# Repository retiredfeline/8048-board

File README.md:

# 8048 board

This is the circuit design for a board using the 8048 MCU, initially intended to be a clock but can be used for other purposes. It can drive multiplexed 7 segment LEDs or a serial interface display using the TM1637 chip. The timer reference can be the onboard crystal, a DS128(8)7 clock chip, or mains.

In retrospect 7407s are probably better for the output buffers because if their input is high or floating, say the 8048 chip is removed, their output transistors will be non-conducting to ground, and less likely to burn out displays.

## Versioning

First release July 2019

## Authors

* **Ken Yap**

## License

See the [LICENSE](LICENSE.md) file for license rights and limitations (MIT).

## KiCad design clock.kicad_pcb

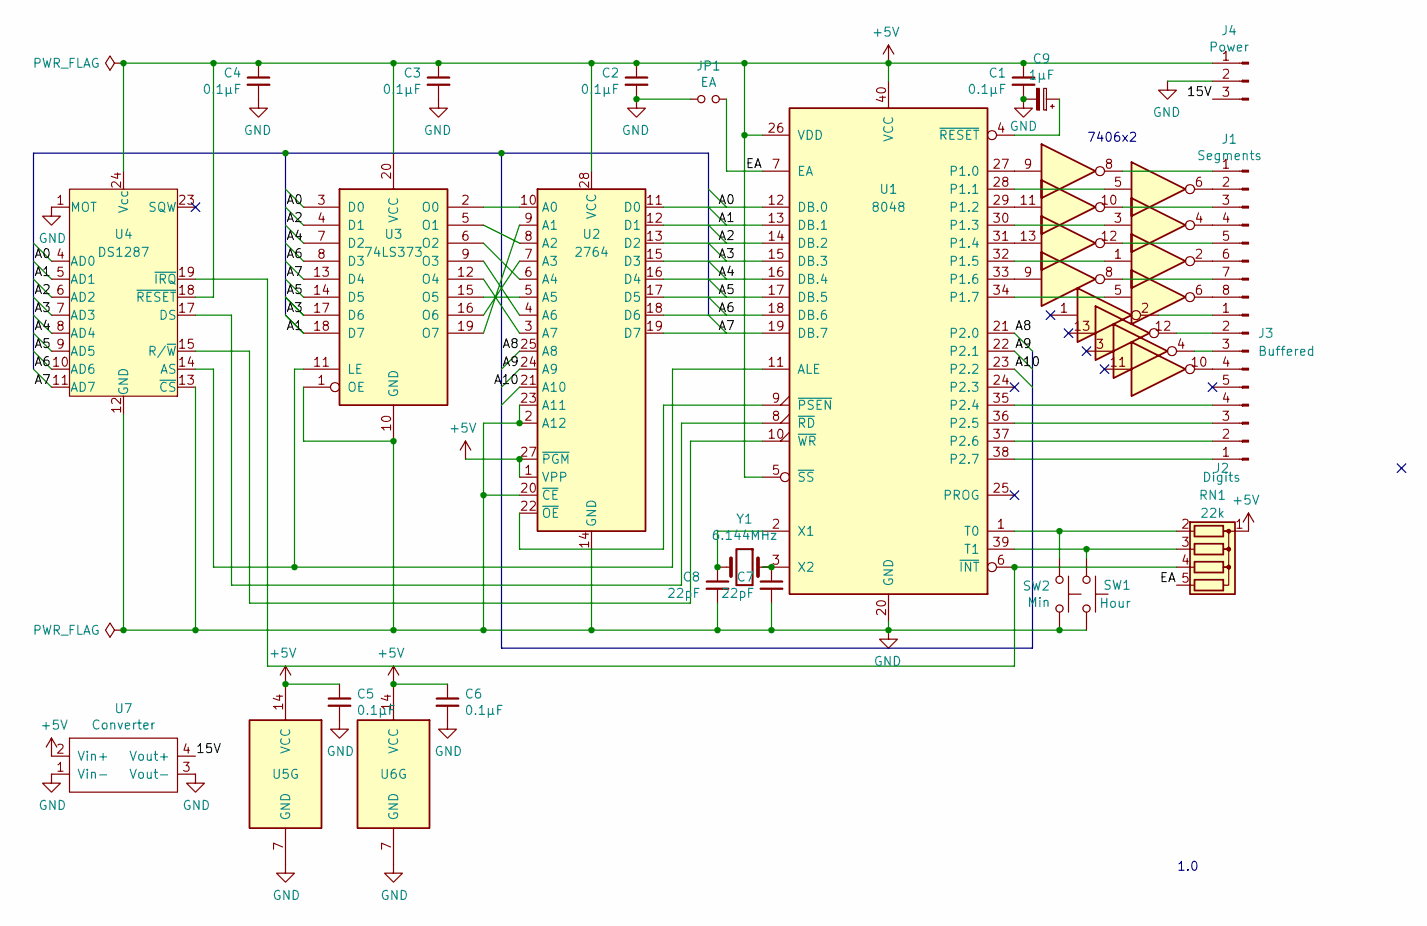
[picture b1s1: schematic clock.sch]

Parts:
C1, C2, C3, C4, C5, C6: 0.1µF; C_Rect_L7.0mm_W2.5mm_P5.00mm
C7, C8: 22pF; C_Disc_D3.0mm_W1.6mm_P2.50mm
C9: 1µF; CP_Radial_D5.0mm_P2.50mm
J1: Segments; PinHeader_1x08_P2.54mm_Vertical
J2: Digits; PinHeader_1x05_P2.54mm_Vertical
J3: Buffered; PinHeader_1x04_P2.54mm_Vertical
J4: Power; PinHeader_1x03_P2.54mm_Vertical
JP1: EA; PinHeader_1x02_P2.54mm_Vertical
RN1: 22k; R_Array_SIP5
SW1: Hour; SW_PUSH_6mm
SW2: Min; SW_PUSH_6mm
U1: 8048; DIP-40_W15.24mm
U2: 2764; DIP-28_W15.24mm
U3: 74LS373; DIP-20_W7.62mm
U4: DS1287; DIP-24_W15.24mm
U5, U6: 74LS06; DIP-14_W7.62mm
U7: Converter; Daughterboard_30.48x17.78_25.40x15.24
Y1: 6.144MHz; Crystal_HC18-U_Vertical

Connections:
+5V: C1.1, C2.1, C3.1, C4.1, C5.1, C6.1, J4.1, RN1.1 (common), U1.5 (~SS~), U1.26 (VDD), U1.40 (VCC), U2.1 (VPP), U2.27 (~PGM), U2.28 (VCC), U3.20 (VCC), U4.18 (~RESET~), U4.24 (Vcc), U5.14 (VCC), U6.14 (VCC), U7.2 (Vin+)
/15V: J4.3, U7.4 (Vout+)
/A0: U1.12 (DB.0), U2.11 (D0), U3.3 (D0), U4.4 (AD0)
/A1: U1.13 (DB.1), U2.12 (D1), U3.18 (D7), U4.5 (AD1)
/A2: U1.14 (DB.2), U2.13 (D2), U3.4 (D1), U4.6 (AD2)
/A3: U1.15 (DB.3), U2.15 (D3), U3.17 (D6), U4.7 (AD3)
/A4: U1.16 (DB.4), U2.16 (D4), U3.7 (D2), U4.8 (AD4)
/A5: U1.17 (DB.5), U2.17 (D5), U3.14 (D5), U4.9 (AD5)
/A6: U1.18 (DB.6), U2.18 (D6), U3.8 (D3), U4.10 (AD6)
/A7: U1.19 (DB.7), U2.19 (D7), U3.13 (D4), U4.11 (AD7)
/A8: U1.21 (P2.0), U2.25 (A8)
/A9: U1.22 (P2.1), U2.24 (A9)
/A10: U1.23 (P2.2), U2.21 (A10)
/EA: JP1.1, RN1.5 (R4), U1.7 (EA)
GND: C1.2, C2.2, C3.2, C4.2, C5.2, C6.2, C7.2, C8.2, C9.2, J4.2, JP1.2, SW1.2, SW2.1, U1.20 (GND), U2.2 (A12), U2.14 (GND), U2.20 (~CE), U2.23 (A11), U3.1 (OE), U3.10 (GND), U4.1 (MOT), U4.12 (GND), U4.13 (~CS~), U5.7 (GND), U6.7 (GND), U7.1 (Vin-), U7.3 (Vout-)
unnamed: C7.1, U1.3 (X2), Y1.1
unnamed: C8.1, U1.2 (X1), Y1.2
unnamed: C9.1, U1.4 (~RESET~)
unnamed: J1.1, U5.8
unnamed: J1.2, U5.6
unnamed: J1.3, U5.10
unnamed: J1.4, U5.4
unnamed: J1.5, U5.12
unnamed: J1.6, U5.2
unnamed: J1.7, U6.8
unnamed: J1.8, U6.6
unnamed: J2.1, U1.38 (P2.7)
unnamed: J2.2, U1.37 (P2.6)
unnamed: J2.3, U1.36 (P2.5)
unnamed: J2.4, U1.35 (P2.4)
unnamed: J3.1, U6.2
unnamed: J3.2, U6.12
unnamed: J3.3, U6.4
unnamed: J3.4, U6.10
unnamed: RN1.2 (R1), SW2.2, U1.1 (T0)
unnamed: RN1.3 (R2), SW1.1, U1.39 (T1)
unnamed: RN1.4 (R3), U1.6 (~INT~), U4.19 (~IRQ~)
unnamed: U1.8 (~RD~), U4.17 (DS)
unnamed: U1.9 (~PSEN~), U2.22 (~OE)
unnamed: U1.10 (~WR~), U4.15 (R/~W~)
unnamed: U1.11 (ALE), U3.11 (LE), U4.14 (AS)
unnamed: U1.27 (P1.0), U5.9
unnamed: U1.28 (P1.1), U5.5
unnamed: U1.29 (P1.2), U5.11
unnamed: U1.30 (P1.3), U5.3
unnamed: U1.31 (P1.4), U5.13
unnamed: U1.32 (P1.5), U5.1
unnamed: U1.33 (P1.6), U6.9
unnamed: U1.34 (P1.7), U6.5
unnamed: U2.3 (A7), U3.12 (O4)
unnamed: U2.4 (A6), U3.9 (O3)
unnamed: U2.5 (A5), U3.15 (O5)
unnamed: U2.6 (A4), U3.6 (O2)
unnamed: U2.7 (A3), U3.16 (O6)
unnamed: U2.8 (A2), U3.5 (O1)
unnamed: U2.9 (A1), U3.19 (O7)
unnamed: U2.10 (A0), U3.2 (O0)

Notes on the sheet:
1.0
7406x2

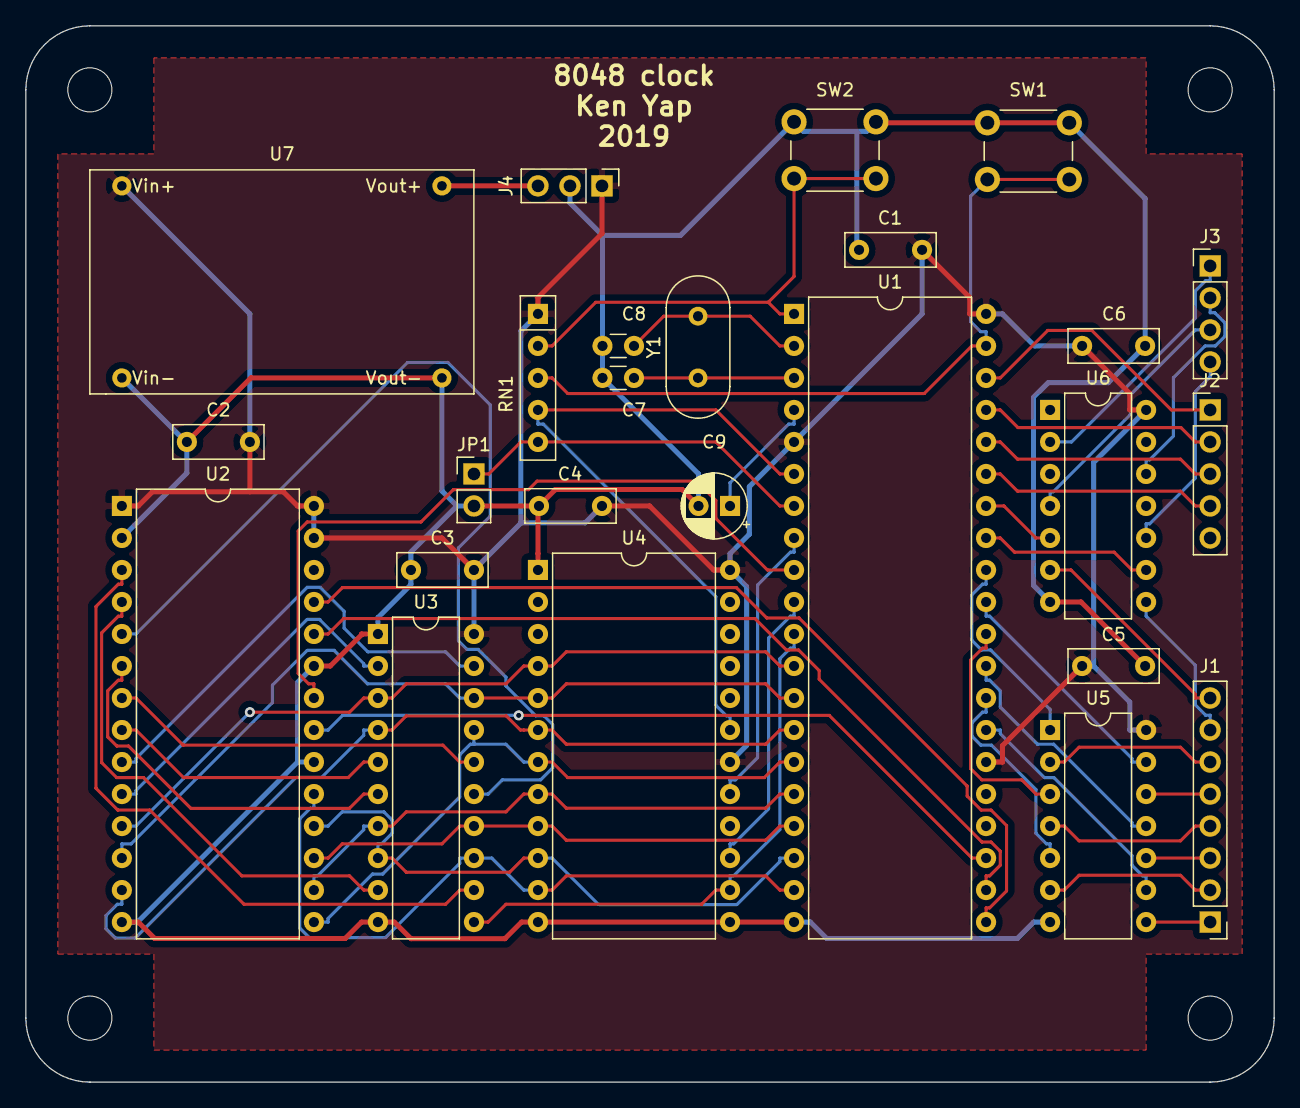
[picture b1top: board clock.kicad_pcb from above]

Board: 2 copper layers, 99.1 x 83.8 mm, 30 parts (1 on the bottom side), 57 nets.

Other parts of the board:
H1, H2, H3, H4: MountingHole_3.5mm
K1: KiCad-Logo_5mm_SilkScreen

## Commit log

2019-07-31 Publish board design
2019-11-15 Add PDF of schematic
2020-01-23 Forgot to include -cache.lib file
2022-04-20 Rename clock to 8048board
2024-11-11 Rotate to landscape
2024-11-15 Note about 7407s instead of 7406s on output
